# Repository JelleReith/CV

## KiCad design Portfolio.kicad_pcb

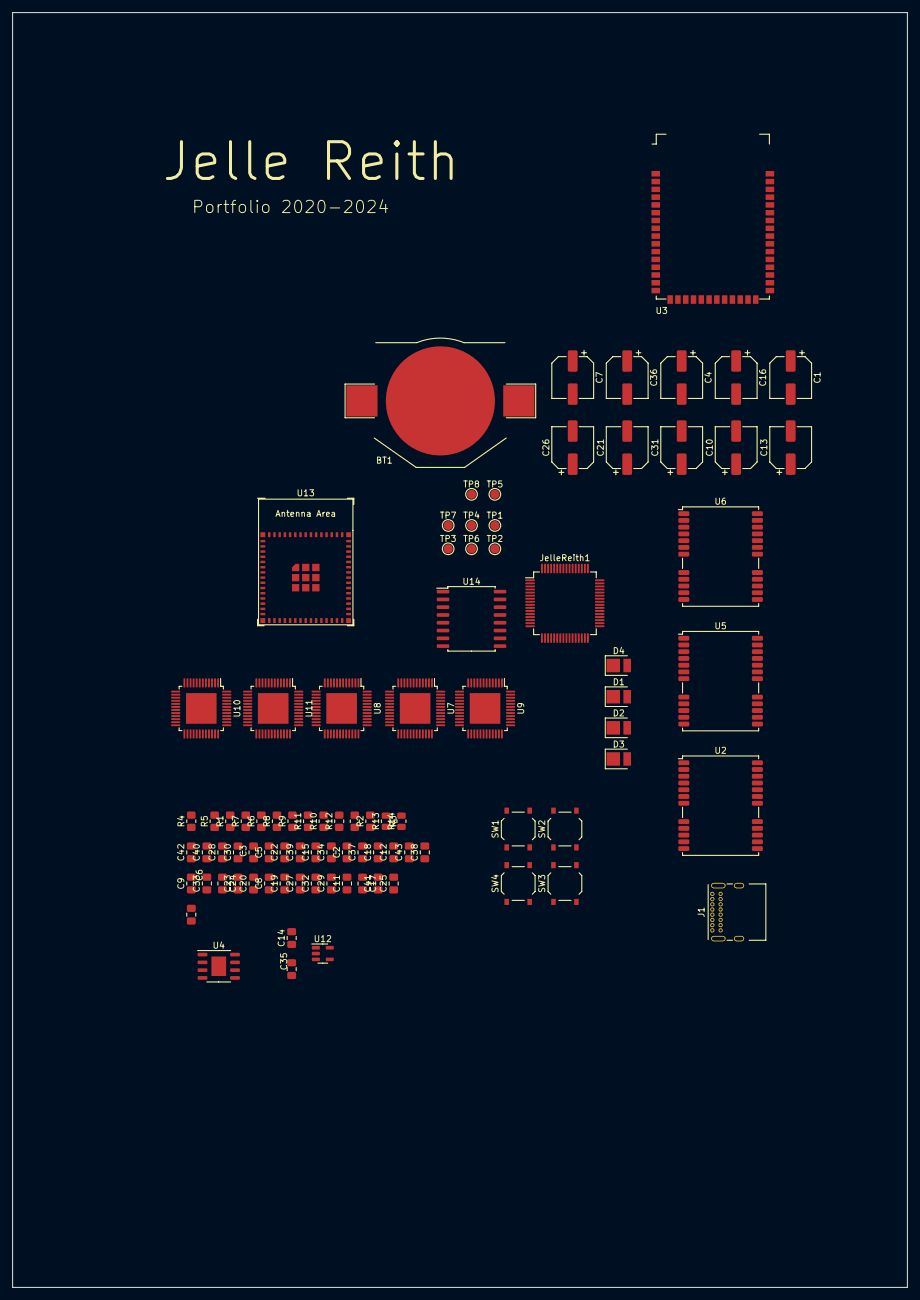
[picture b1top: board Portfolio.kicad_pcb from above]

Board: 2 copper layers, 146.0 x 208.0 mm, 89 parts (0 on the bottom side), 53 nets, no tracks yet.

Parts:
BT1: Battery_Cell; BatteryHolder_Keystone_3002_1x2032
C1, C4, C7, C10, C13, C16, C21, C26, C31, C36: C_Polarized; CP_Elec_6.3x7.7
C2, C5, C8, C11, C14, C18, C20, C23, C25, C28, C30, C33, C35, C38, C40: 0.1uF; C_0805_2012Metric_Pad1.18x1.45mm_HandSolder
C3, C6, C9, C12, C15, C17, C19, C22, C24, C27, C29, C32, C34, C37, C39: 0.47uF; C_0805_2012Metric_Pad1.18x1.45mm_HandSolder
C41, C42: 22uF; C_0805_2012Metric_Pad1.18x1.45mm_HandSolder
C43: 1uF; C_0805_2012Metric_Pad1.18x1.45mm_HandSolder
D1, D2, D3, D4: LED; LED_PLCC_2835
J1: USB_C_Receptacle_USB2.0; USB_C_Receptacle_GCT_USB4085
JelleReith1: STM32G491RETx; LQFP-64_10x10mm_P0.5mm
R1, R2, R3, R4, R5: 20K; R_0805_2012Metric_Pad1.20x1.40mm_HandSolder
R6, R7, R8: 5.1K; R_0805_2012Metric_Pad1.20x1.40mm_HandSolder
R9, R10, R11, R12: 10K; R_0805_2012Metric_Pad1.20x1.40mm_HandSolder
R13, R14: 2k; R_0805_2012Metric
SW1, SW2, SW3, SW4: SW_Push; SW_Push_1P1T_XKB_TS-1187A
TP1, TP2, TP3, TP4, TP5, TP6, TP7, TP8: TestPoint; TestPoint_Pad_D1.5mm
U2, U5, U6: NEO-M8N; ublox_NEO
U3: USR-C322
U4: BD90FC0WEFJ; HTSOP-8-1EP_3.9x4.9mm_P1.27mm_EP2.4x3.2mm
U7, U8, U9, U10, U11: IS31FL3733-TQ; TQFP-48-1EP_7x7mm_P0.5mm_EP5x5mm
U12: AP2112K-3.3; SOT-23-5
U13: ESP32-S3-MINI-1
U14: DS3231M; SOIC-16W_7.5x10.3mm_P1.27mm

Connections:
3V3: C42.1, R8.1, R13.2, R14.2, TP4.1, TP8.1, U7.39 (VIO), U7.43 (ADDR1), U7.46 (~SDB), U8.39 (VIO), U8.46 (~SDB), U9.39 (VIO), U9.46 (~SDB), U10.39 (VIO), U10.46 (~SDB), U11.39 (VIO), U11.46 (~SDB), U12.5 (VOUT), U13.3 (3V3), U14.2 (VCC)
BOOT: SW2.1, U13.4 (GPIO0/BOOT)
EN: C43.1, R8.2, SW1.1, U4.5 (EN), U13.45 (EN)
FUTURE_LED: R10.1, U13.8 (GPIO4/TOUCH4/ADC1_CH3)
FUTURE_LED_LINE: D2.2 (A), R10.2
GND: BT1.2 (-), C1.2, C2.2, C3.2, C4.2, C5.2, C6.2, C7.2, C8.2, C9.2, C10.2, C11.2, C12.2, C13.2, C14.2, C15.2, C16.2, C17.2, C18.2, C19.2, C20.2, C21.2, C22.2, C23.2, C24.2, C25.2, C26.2, C27.2, C28.2, C29.2, C30.2, C31.2, C32.2, C33.2, C34.2, C35.2, C36.2, C37.2, C38.2, C39.2, C40.2, C41.2, C42.2, C43.2, D1.1 (K), D2.1 (K), D3.1 (K), D4.1 (K), J1.A1 (GND), J1.A12 (GND), J1.B1 (GND), J1.B12 (GND), J1.S1 (SHIELD), JelleReith1.15 (VSS), JelleReith1.16 (VDD), JelleReith1.27 (VSSA), JelleReith1.29 (VDDA), JelleReith1.31 (VSS), JelleReith1.32 (VDD), JelleReith1.47 (VSS), JelleReith1.48 (VDD), JelleReith1.63 (VSS), JelleReith1.64 (VDD), R1.1, R2.1, R3.1, R4.1, R5.1, R6.2, R7.2, SW1.2, SW2.2, SW3.1, SW4.1, TP1.1, TP5.1, U2.10 (GND), U2.12 (GND), U2.13 (GND), U2.24 (GND), U3.1 (GND), U3.11 (GND), U3.12 (GND), U3.17 (GND), U3.28 (GND), U3.29 (GND), U3.44 (GND), U4.3 (GND), U4.9 (GND), U7.5 (PGND), U7.12 (PGND), U7.34 (AGND), U7.44 (ADDR2), U7.47 (IICRST), U7.48 (GND), U7.49 (GND), U8.5 (PGND), U8.12 (PGND), U8.34 (AGND), U8.43 (ADDR1), U8.47 (IICRST), U8.48 (GND), U8.49 (GND), U9.5 (PGND), U9.12 (PGND), U9.34 (AGND), U9.44 (ADDR2), U9.47 (IICRST), U9.48 (GND), U9.49 (GND), U10.5 (PGND), U10.12 (PGND), U10.34 (AGND), U10.44 (ADDR2), U10.47 (IICRST), U10.48 (GND), U10.49 (GND), U11.5 (PGND), U11.12 (PGND), U11.34 (AGND), U11.43 (ADDR1), U11.44 (ADDR2), U11.47 (IICRST), U11.48 (GND), U11.49 (GND), U12.2 (GND), U13.1 (GND), U13.2 (GND), U13.42 (GND), U13.43 (GND), U13.46 (GND), U13.47 (GND), U13.48 (GND), U13.49 (GND), U13.50 (GND), U13.51 (GND), U13.52 (GND), U13.53 (GND), U13.54 (GND), U13.55 (GND), U13.56 (GND), U13.57 (GND), U13.58 (GND), U13.59 (GND), U13.60 (GND), U13.61 (GND), U13.62 (GND), U13.63 (GND), U13.64 (GND), U13.65 (GND), U14.5 (GND), U14.6 (GND), U14.7 (GND), U14.8 (GND), U14.9 (GND), U14.10 (GND), U14.11 (GND), U14.12 (GND), U14.13 (GND)
I2C_SCL: R13.1, U7.42 (SCL), U8.42 (SCL), U8.44 (ADDR2), U9.42 (SCL), U9.43 (ADDR1), U10.42 (SCL), U11.42 (SCL), U13.39 (U0TXD/GPIO43/CLK_OUT1), U14.16 (SCL)
I2C_SDA: R14.1, U7.41 (SDA), U8.41 (SDA), U9.41 (SDA), U10.41 (SDA), U10.43 (ADDR1), U11.41 (SDA), U13.40 (U0RXD/GPIO44/CLK_OUT2), U14.15 (SDA)
LATITUDE_POT_IN: TP6.1, U13.12 (GPIO8/TOUCH8/ADC1_CH7/SUBSPICS1)
LATITUDE_POT_IN_BACKUP: TP7.1, U13.14 (GPIO10/TOUCH10/ADC1_CH9/FSPICS0/FSPIIO4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)
LONGITUDE_POT_IN: TP2.1, U13.11 (GPIO7/TOUCH7/ADC1_CH6)
LONGITUDE_POT_IN_BACKUP: TP3.1, U13.13 (GPIO9/TOUCH9/ADC1_CH8/FSPIHD/SUBSPIHD)
MODE_BUTTON: SW3.2, U13.5 (GPIO1/TOUCH1/ADC1_CH0)
unnamed: BT1.1 (+), U14.14 (VBAT)
unnamed: J1.A5 (CC1), R6.1
unnamed: J1.B5 (CC2), R7.1
unnamed: JelleReith1.12 (PA0), U2.5 (USB_DM), U5.5 (USB_DM), U6.5 (USB_DM)
unnamed: JelleReith1.13 (PA1), U2.6 (USB_DP), U5.6 (USB_DP), U6.6 (USB_DP)
unnamed: JelleReith1.14 (PA2), U2.20 (TXD/SPI_MISO), U5.20 (TXD/SPI_MISO), U6.20 (TXD/SPI_MISO)
unnamed: JelleReith1.17 (PA3), U3.4 (~RESET), U5.18 (SDA/~SPI_CS), U6.21 (RXD/SPI_MOSI)
unnamed: JelleReith1.18 (PA4), U3.21 (~RELOAD)
unnamed: JelleReith1.19 (PA5), U3.22 (~READY)
unnamed: JelleReith1.20 (PA6), U3.23 (~LINK)
unnamed: JelleReith1.21 (PA7), U3.7 (SOP0)
unnamed: JelleReith1.42 (PA8), U3.6 (SOP1)
unnamed: JelleReith1.43 (PA9), U3.5 (SOP2)
unnamed: JelleReith1.44 (PA10), U3.8 (ANA_DC-DC)
unnamed: JelleReith1.8 (PC0), U3.19 (UART0_TX)
unnamed: JelleReith1.9 (PC1), U3.20 (UART0_RX)
unnamed: JelleReith1.10 (PC2), U3.24 (UART0_CTS)
unnamed: JelleReith1.22 (PC4), U3.25 (UART0_RTS)
unnamed: U2.14 (LNA_EN), U3.37 (GPIO11), U5.14 (LNA_EN), U6.14 (LNA_EN)
unnamed: U2.11 (RF_IN), U3.38 (GPIO12), U3.41 (GPIO13), U5.11 (RF_IN), U6.11 (RF_IN)
unnamed: U2.3 (TIMEPULSE), U3.36 (GPIO10), U5.3 (TIMEPULSE), U6.3 (TIMEPULSE)
unnamed: U5.10 (GND), U5.12 (GND), U5.13 (GND), U5.24 (GND)
unnamed: U6.10 (GND), U6.12 (GND), U6.13 (GND), U6.24 (GND)
unnamed: R1.2, U7.35 (RSET)
unnamed: R2.2, U8.35 (RSET)
unnamed: R3.2, U9.35 (RSET)
unnamed: R4.2, U10.35 (RSET)
unnamed: R5.2, U11.35 (RSET)
SECONDARY_LOCATION_LED: R12.1, U13.10 (GPIO6/TOUCH6/ADC1_CH5)
SECONDARY_LOCATION_LED_LINE: D4.2 (A), R12.2
SELECT_BUTTON: SW4.2, U13.6 (GPIO2/TOUCH2/ADC1_CH1)
SOLARGRAPH_LED: R11.1, U13.9 (GPIO5/TOUCH5/ADC1_CH4)
SOLARGRAPH_LED_LINE: D3.2 (A), R11.2
SOLSTICE_EQUINOX_LED: R9.1, U13.7 (GPIO3/TOUCH3/ADC1_CH2)
SOLSTICE_LED_LINE: D1.2 (A), R9.2
SYNC: U7.40 (SYNC), U8.40 (SYNC), U9.40 (SYNC), U10.40 (SYNC), U11.40 (SYNC)
USB_D+: J1.A6 (D+), J1.B6 (D+), U13.24 (GPIO20/U1CTS/ADC2_CH9/CLK_OUT1/USB_D+)
USB_D-: J1.A7 (D-), J1.B7 (D-), U13.23 (GPIO19/U1RTS/ADC2_CH8/CLK_OUT2/USB_D-)
VCC: JelleReith1.1 (VBAT), JelleReith1.28 (VREF+), U4.1 (VO)
V_USB: C1.1, C2.1, C3.1, C4.1, C5.1, C6.1, C7.1, C8.1, C9.1, C10.1, C11.1, C12.1, C13.1, C14.1, C15.1, C16.1, C17.1, C18.1, C19.1, C20.1, C21.1, C22.1, C23.1, C24.1, C25.1, C26.1, C27.1, C28.1, C29.1, C30.1, C31.1, C32.1, C33.1, C34.1, C35.1, C36.1, C37.1, C38.1, C39.1, C40.1, C41.1, J1.A4 (VBUS), J1.A9 (VBUS), J1.B4 (VBUS), J1.B9 (VBUS), U7.20 (PVCC), U7.29 (PVCC), U7.37 (AVCC), U7.38 (DVCC), U8.20 (PVCC), U8.29 (PVCC), U8.37 (AVCC), U8.38 (DVCC), U9.20 (PVCC), U9.29 (PVCC), U9.37 (AVCC), U9.38 (DVCC), U10.20 (PVCC), U10.29 (PVCC), U10.37 (AVCC), U10.38 (DVCC), U11.20 (PVCC), U11.29 (PVCC), U11.37 (AVCC), U11.38 (DVCC), U12.1 (VIN), U12.3 (EN)

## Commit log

2024-04-03 init
2024-11-29 mondriaan voorblad
